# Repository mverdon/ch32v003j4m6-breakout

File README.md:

# CH32V003J4M6 Breakout Board

This is a simple breakout board for prototyping with the CH32V003 MCU.
It uses the SOP-8 variant (CH32V003J4M6) so that it can be easily hand
soldered.

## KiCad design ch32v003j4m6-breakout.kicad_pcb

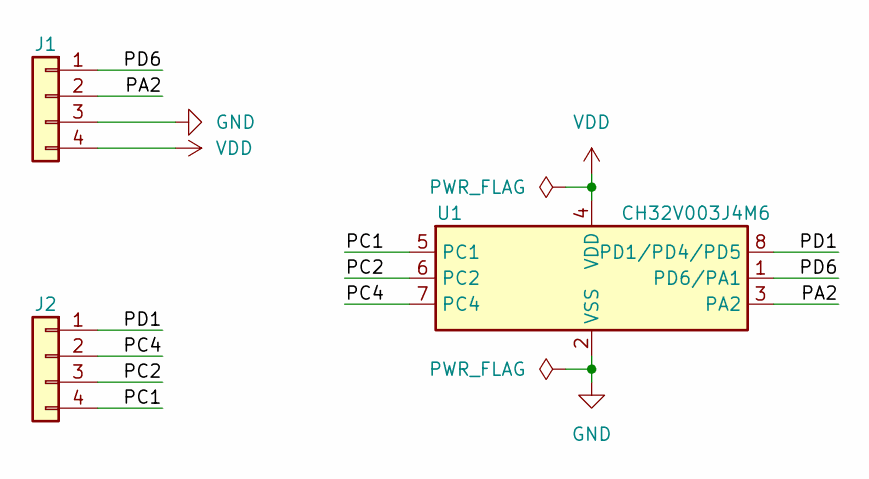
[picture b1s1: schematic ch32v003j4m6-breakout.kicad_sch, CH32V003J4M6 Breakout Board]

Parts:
J1, J2: Conn_01x04; PinHeader_1x04_P2.54mm_Vertical
U1: CH32V003J4M6; SOP-8_3.9x4.9mm_P1.27mm

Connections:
/PA2: J1.2, U1.3 (PA2)
/PC1: J2.4, U1.5 (PC1)
/PC2: J2.3, U1.6 (PC2)
/PC4: J2.2, U1.7 (PC4)
/PD1: J2.1, U1.8 (PD1/PD4/PD5)
/PD6: J1.1, U1.1 (PD6/PA1)
GND: J1.3, U1.2 (VSS)
VDD: J1.4, U1.4 (VDD)

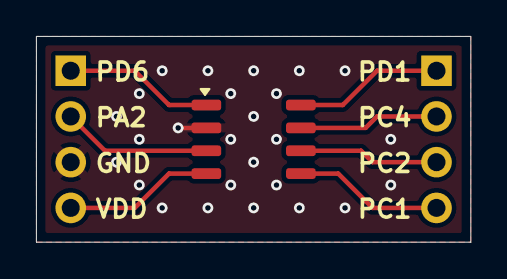
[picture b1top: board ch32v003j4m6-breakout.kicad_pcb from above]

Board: 2 copper layers, 24.1 x 11.4 mm, 3 parts (0 on the bottom side), 8 nets.

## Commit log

2025-04-05 feat(ci): add CI validation and build scripts
2025-04-05 fix: exclude headers from BOM
2025-04-05 feat(ci): add GitHub action for validation step
2025-04-05 feat(ci): attempt to solve permission access error on checkout
2025-04-05 feat(ci): add option to use root user
2025-04-05 feat(ci): fix syntax
2025-04-05 feat(ci): attempt with user kicad
2025-04-05 feat(ci): set up KiCad for root user
2025-04-05 feat(ci): save latest ERC/DRC reports, keep them for 1 day
2025-04-05 fix: add missing symbol library `power` to project-specific libraries
2025-04-05 feat(ci): remove setup step
2025-04-05 feat(ci): build board files when a tag is pushed
2025-04-05 feat(ci): remove push check, replace artifact upload with release creation
2025-04-05 feat(ci): add token for release step
2025-04-05 feat(ci): add specific permissions required to create a release
